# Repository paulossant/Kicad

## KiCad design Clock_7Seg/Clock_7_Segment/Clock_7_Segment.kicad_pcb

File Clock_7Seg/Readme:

PCB files for the clock seven segment displays

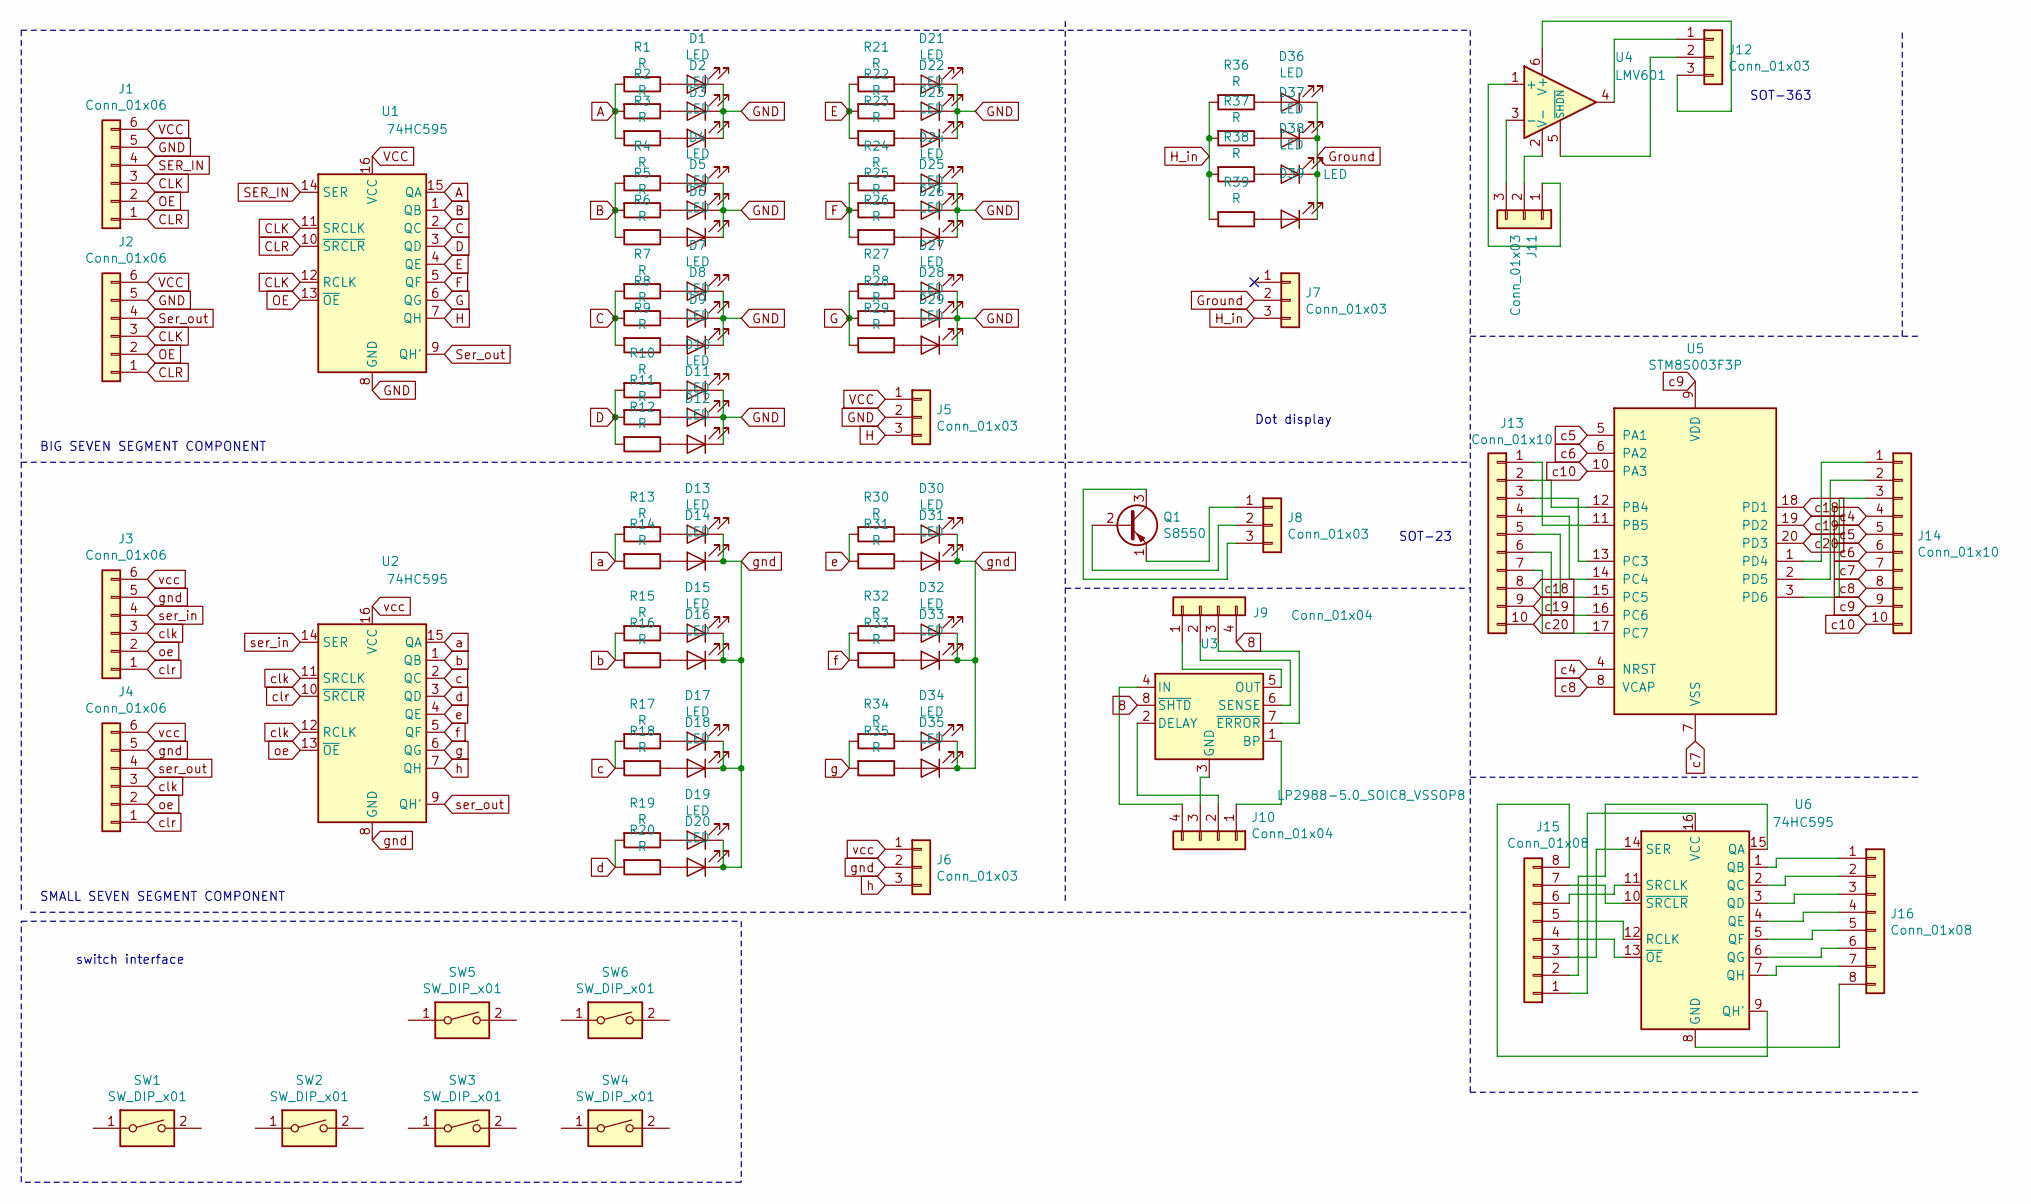
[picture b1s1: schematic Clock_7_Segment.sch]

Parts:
D1, D2, D3, D4, D5, D6, D7, D8, D9, D10, D11, D12, D13, D14, D15, D16, D17, D18, D19, D20, D21, D22, D23, D24, D25, D26, D27, D28, D29, D30, D31, D32, D33, D34, D35, D36, D37, D38, D39: LED; LED_0805_2012Metric_Pad1.15x1.40mm_HandSolder
J1, J2, J3, J4: Conn_01x06; PinHeader_1x06_P2.54mm_Vertical
J5, J6, J7, J8, J11, J12: Conn_01x03; PinHeader_1x03_P2.54mm_Vertical
J9, J10: Conn_01x04; PinHeader_1x04_P2.54mm_Vertical
J13, J14: Conn_01x10; PinHeader_1x10_P2.54mm_Vertical
J15, J16: Conn_01x08; PinHeader_1x08_P2.54mm_Vertical
Q1: S8550; SOT-23
R1, R2, R3, R4, R5, R6, R7, R8, R9, R10, R11, R12, R13, R14, R15, R16, R17, R18, R19, R20, R21, R22, R23, R24, R25, R26, R27, R28, R29, R30, R31, R32, R33, R34, R35, R36, R37, R38, R39: R; R_0805_2012Metric_Pad1.15x1.40mm_HandSolder
SW1, SW2, SW3, SW4, SW5, SW6: SW_DIP_x01; SW_PUSH_6mm_H4.3mm
U1, U2, U6: 74HC595; SOIC-16_3.9x9.9mm_P1.27mm
U3: LP2988-5.0_SOIC8_VSSOP8; SOIC-8-1EP_3.9x4.9mm_P1.27mm_EP2.95x4.9mm_Mask2.71x3.4mm
U4: LMV601; SOT-363_SC-70-6
U5: STM8S003F3P; TSSOP-20_4.4x6.5mm_P0.65mm

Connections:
8: J9.4, U3.8 (~SHTD)
A: R1.2, R2.2, R3.2, U1.15 (QA)
B: R4.2, R5.2, R6.2, U1.1 (QB)
C: R7.2, R8.2, R9.2, U1.2 (QC)
CLK: J1.3, J2.3, U1.11 (SRCLK), U1.12 (RCLK)
CLR: J1.1, J2.1, U1.10 (~SRCLR)
D: R10.2, R11.2, R12.2, U1.3 (QD)
E: R21.2, R22.2, R23.2, U1.4 (QE)
F: R24.2, R25.2, R26.2, U1.5 (QF)
G: R27.2, R28.2, R29.2, U1.6 (QG)
GND: D1.1 (K), D2.1 (K), D3.1 (K), D4.1 (K), D5.1 (K), D6.1 (K), D7.1 (K), D8.1 (K), D9.1 (K), D10.1 (K), D11.1 (K), D12.1 (K), D21.1 (K), D22.1 (K), D23.1 (K), D24.1 (K), D25.1 (K), D26.1 (K), D27.1 (K), D28.1 (K), D29.1 (K), J1.5, J2.5, J5.2, U1.8 (GND)
Ground: D36.1 (K), D37.1 (K), D38.1 (K), D39.1 (K), J7.2
H: J5.3, U1.7 (QH)
H_in: J7.3, R36.2, R37.2, R38.2, R39.2
unnamed: D1.2 (A), R1.1
unnamed: D2.2 (A), R2.1
unnamed: D3.2 (A), R3.1
unnamed: D4.2 (A), R4.1
unnamed: D5.2 (A), R5.1
unnamed: D6.2 (A), R6.1
unnamed: D7.2 (A), R7.1
unnamed: D8.2 (A), R8.1
unnamed: D9.2 (A), R9.1
unnamed: D10.2 (A), R10.1
unnamed: D11.2 (A), R11.1
unnamed: D12.2 (A), R12.1
unnamed: D13.2 (A), R13.1
unnamed: D14.2 (A), R14.1
unnamed: D15.2 (A), R15.1
unnamed: D16.2 (A), R16.1
unnamed: D17.2 (A), R17.1
unnamed: D18.2 (A), R18.1
unnamed: D19.2 (A), R19.1
unnamed: D20.2 (A), R20.1
unnamed: D21.2 (A), R21.1
unnamed: D22.2 (A), R22.1
unnamed: D23.2 (A), R23.1
unnamed: D24.2 (A), R24.1
unnamed: D25.2 (A), R25.1
unnamed: D26.2 (A), R26.1
unnamed: D27.2 (A), R27.1
unnamed: D28.2 (A), R28.1
unnamed: D29.2 (A), R29.1
unnamed: D30.2 (A), R30.1
unnamed: D31.2 (A), R31.1
unnamed: D32.2 (A), R32.1
unnamed: D33.2 (A), R33.1
unnamed: D34.2 (A), R34.1
unnamed: D35.2 (A), R35.1
unnamed: D36.2 (A), R36.1
unnamed: D37.2 (A), R37.1
unnamed: D38.2 (A), R38.1
unnamed: D39.2 (A), R39.1
unnamed: J8.1, Q1.1 (E)
unnamed: J8.2, Q1.2 (B)
unnamed: J8.3, Q1.3 (C)
unnamed: J9.1, U3.5 (OUT)
unnamed: J9.2, U3.6 (SENSE)
unnamed: J9.3, U3.7 (~ERROR)
unnamed: J10.1, U3.1 (BP)
unnamed: J10.2, U3.2 (DELAY)
unnamed: J10.3, U3.3 (GND)
unnamed: J10.4, U3.4 (IN)
unnamed: J11.1, U4.1 (+)
unnamed: J11.2, U4.2 (V-)
unnamed: J11.3, U4.3 (-)
unnamed: J12.1, U4.4
unnamed: J12.2, U4.5 (~SHDN)
unnamed: J12.3, U4.6 (V+)
unnamed: J13.1, U5.11 (PB5)
unnamed: J13.2, U5.12 (PB4)
unnamed: J13.3, U5.13 (PC3)
unnamed: J13.4, U5.14 (PC4)
unnamed: J13.5, U5.15 (PC5)
unnamed: J13.6, U5.16 (PC6)
unnamed: J13.7, U5.17 (PC7)
unnamed: J14.1, U5.1 (PD4)
unnamed: J14.2, U5.2 (PD5)
unnamed: J14.3, U5.3 (PD6)
unnamed: J15.1, U6.16 (VCC)
unnamed: J15.2, U6.15 (QA)
unnamed: J15.3, U6.14 (SER)
unnamed: J15.4, U6.13 (~OE)
unnamed: J15.5, U6.12 (RCLK)
unnamed: J15.6, U6.11 (SRCLK)
unnamed: J15.7, U6.10 (~SRCLR)
unnamed: J15.8, U6.9 (QH')
unnamed: J16.1, U6.1 (QB)
unnamed: J16.2, U6.2 (QC)
unnamed: J16.3, U6.3 (QD)
unnamed: J16.4, U6.4 (QE)
unnamed: J16.5, U6.5 (QF)
unnamed: J16.6, U6.6 (QG)
unnamed: J16.7, U6.7 (QH)
unnamed: J16.8, U6.8 (GND)
OE: J1.2, J2.2, U1.13 (~OE)
SER_IN: J1.4, U1.14 (SER)
Ser_out: J2.4, U1.9 (QH')
VCC: J1.6, J2.6, J5.1, U1.16 (VCC)
a: R13.2, R14.2, U2.15 (QA)
b: R15.2, R16.2, U2.1 (QB)
c: R17.2, R18.2, U2.2 (QC)
c4: J14.4, U5.4 (NRST)
c5: J14.5, U5.5 (PA1)
c6: J14.6, U5.6 (PA2)
c7: J14.7, U5.7 (VSS)
c8: J14.8, U5.8 (VCAP)
c9: J14.9, U5.9 (VDD)
c10: J14.10, U5.10 (PA3)
c18: J13.8, U5.18 (PD1)
c19: J13.9, U5.19 (PD2)
c20: J13.10, U5.20 (PD3)
clk: J3.3, J4.3, U2.11 (SRCLK), U2.12 (RCLK)
clr: J3.1, J4.1, U2.10 (~SRCLR)
d: R19.2, R20.2, U2.3 (QD)
e: R30.2, R31.2, U2.4 (QE)
f: R32.2, R33.2, U2.5 (QF)
g: R34.2, R35.2, U2.6 (QG)
gnd: D13.1 (K), D14.1 (K), D15.1 (K), D16.1 (K), D17.1 (K), D18.1 (K), D19.1 (K), D20.1 (K), D30.1 (K), D31.1 (K), D32.1 (K), D33.1 (K), D34.1 (K), D35.1 (K), J3.5, J4.5, J6.2, U2.8 (GND)
h: J6.3, U2.7 (QH)
oe: J3.2, J4.2, U2.13 (~OE)
ser_in: J3.4, U2.14 (SER)
ser_out: J4.4, U2.9 (QH')
vcc: J3.6, J4.6, J6.1, U2.16 (VCC)

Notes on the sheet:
BIG SEVEN SEGMENT COMPONENT
SMALL SEVEN SEGMENT COMPONENT
Dot display
SOT-23
SOT-363
switch interface

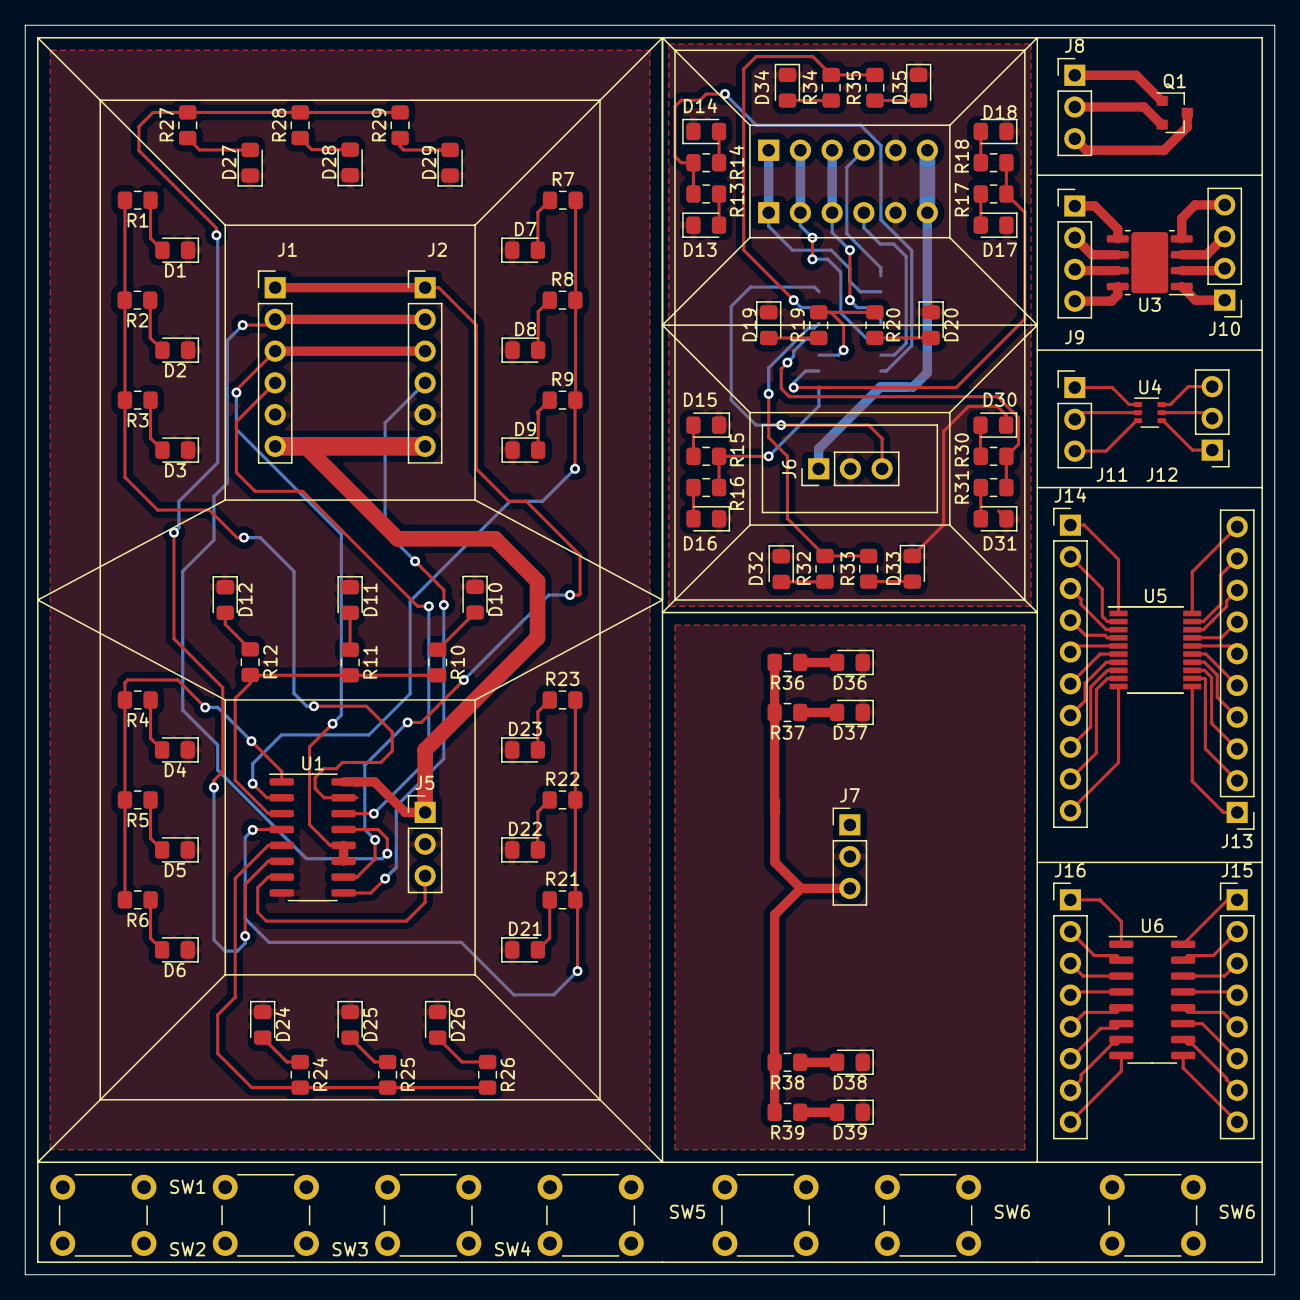
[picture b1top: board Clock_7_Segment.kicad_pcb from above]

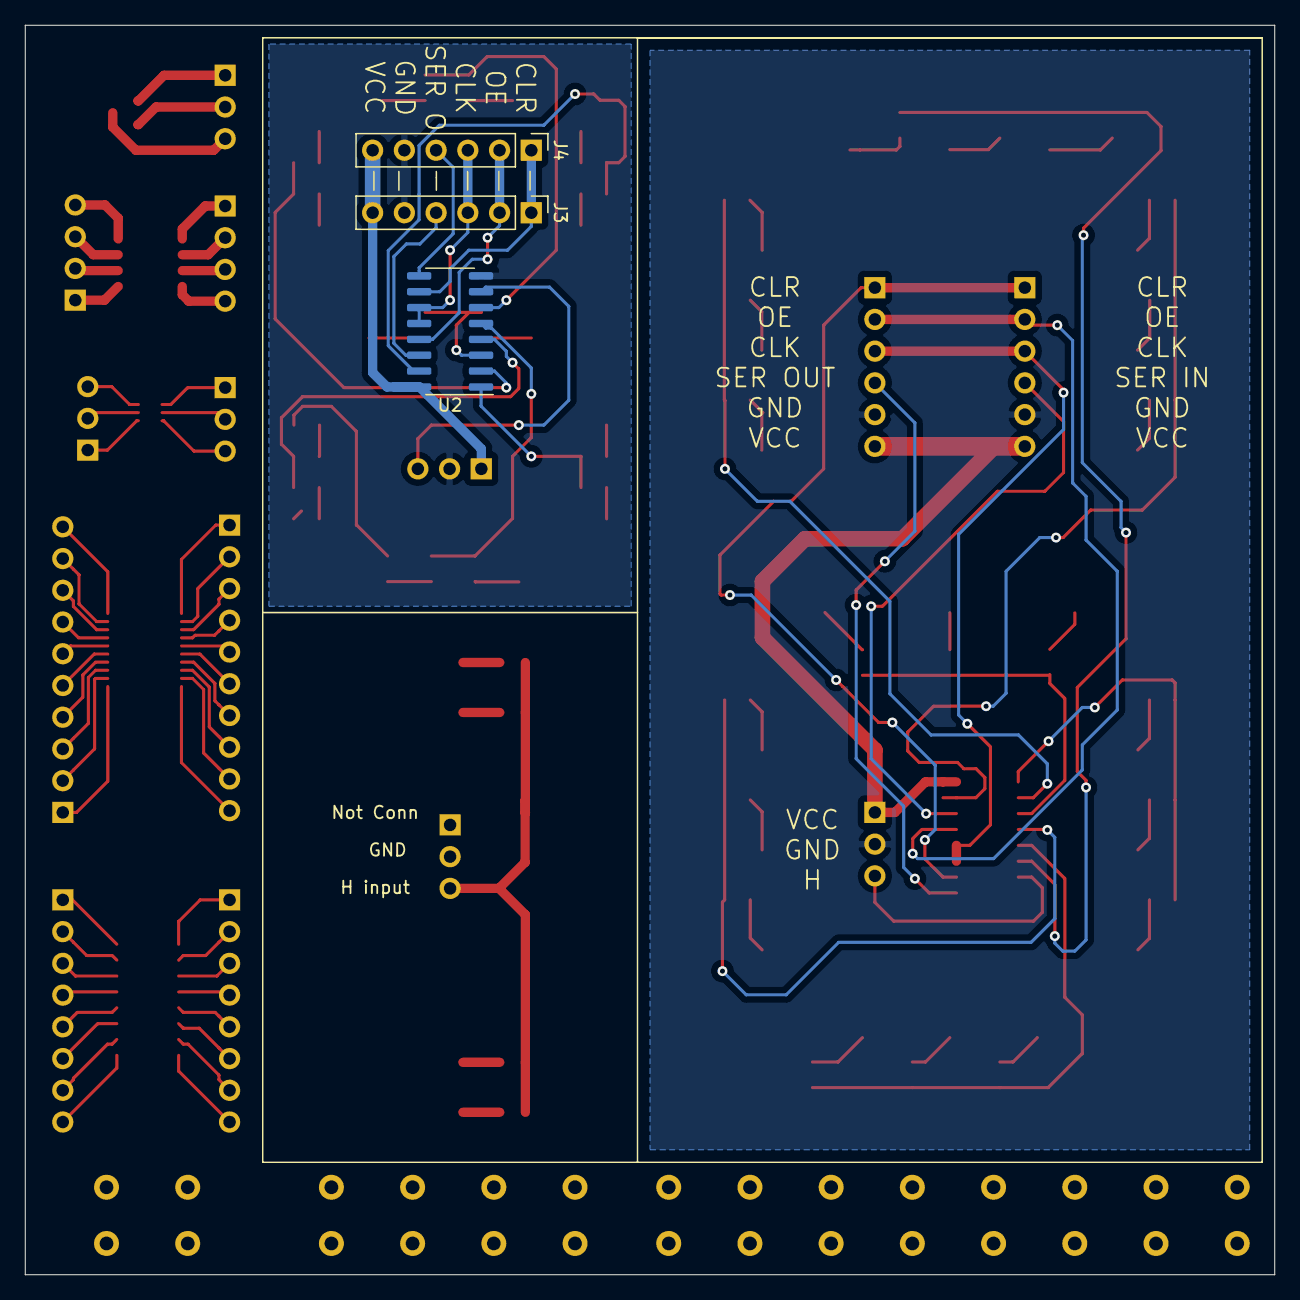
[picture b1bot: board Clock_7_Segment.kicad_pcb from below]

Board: 2 copper layers, 100.0 x 100.0 mm, 108 parts (3 on the bottom side), 124 nets.

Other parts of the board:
SW6#2: SW_DIP_x01; SW_PUSH_6mm_H4.3mm

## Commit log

2019-06-13 Add files via upload
    added first sketch
2019-06-13 Add files via upload
    updated qfnp48 header pins to 02x06
2019-06-27 Add files via upload
    work in progress
2019-06-28 Add files via upload
    First completed version
2019-07-15 Add files via upload
    REV 1.0
    Through holes components
2019-07-16 uploaded all the available libraries
    will need the removal or adding of some files in the future.
2019-07-16 Through Hole to SMD components
    first print of the board
